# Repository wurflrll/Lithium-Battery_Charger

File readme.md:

# (Cascaded) Lithium-Ion Battery Charger 

The goals is a modular design for charging a lithium ion battery.  The board has two parts, the actual charging circuitry and the communication peripherals.

The communication peripherals includes an electrically isolated UART interface over a pulse transformer, an I2C interface to talk to the board's DAC module, and some general purpose inputs and outputs. 

Power Supply: 12V

V1 had a few issues, one was a layout error with the PIC microcontroller (I created the symbols itself in KiCad).  The other issue, much more interesting, is an issue with stability in the constant current controller.

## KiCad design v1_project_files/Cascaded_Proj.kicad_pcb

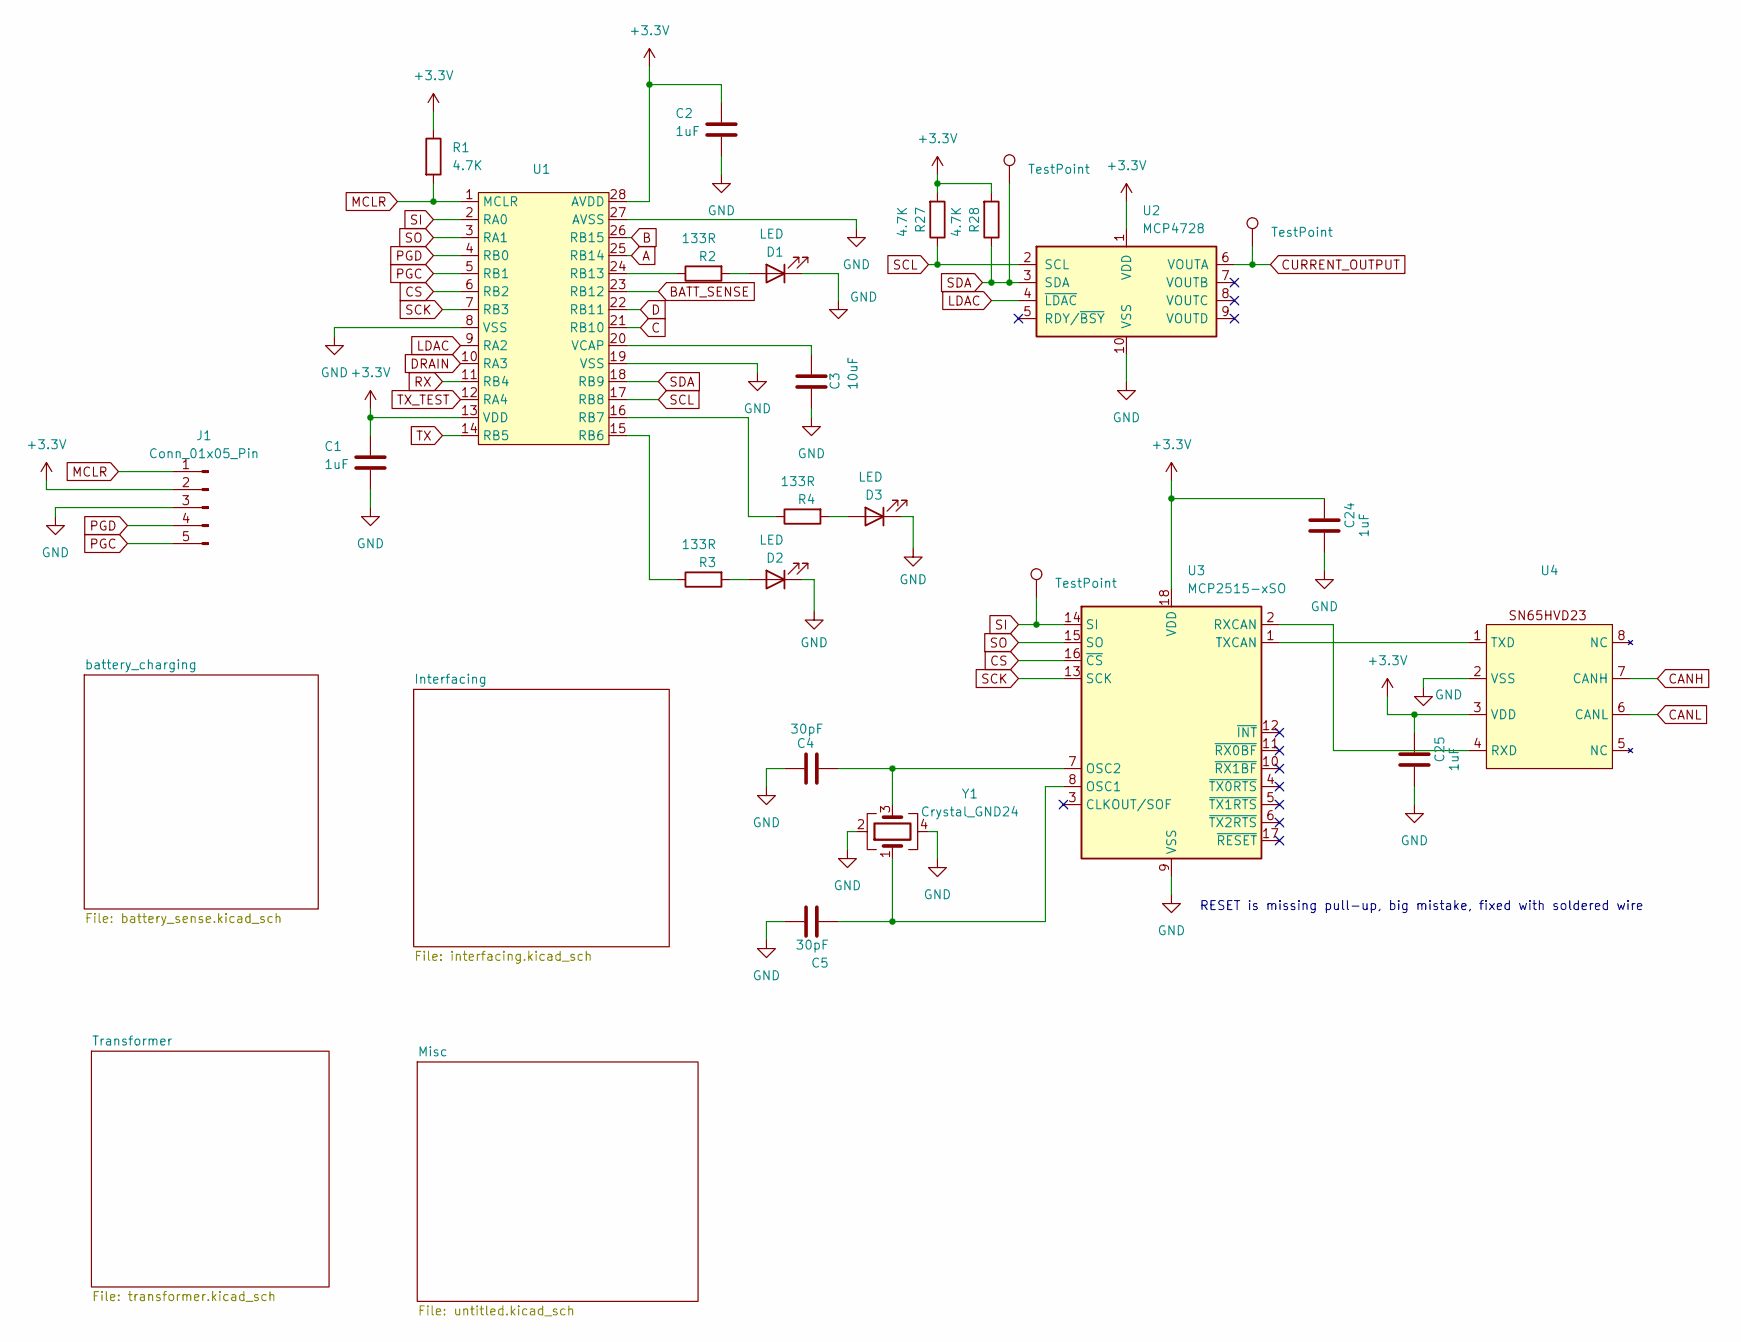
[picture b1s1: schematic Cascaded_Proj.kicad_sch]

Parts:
C1, C2, C24, C25: 1uF; C_0603_1608Metric
C3: 10uF; C_0603_1608Metric
C4, C5: 30pF; C_0603_1608Metric
D1, D2, D3: LED; LED_0805_2012Metric
J1: Conn_01x05_Pin; PinHeader_1x05_P2.54mm_Vertical
R1, R27, R28: 4.7K; R_0603_1608Metric
R2, R3, R4: 133R; R_0603_1608Metric
TP5, TP6, TP7: TestPoint; TestPoint_Plated_Hole_D2.0mm
U1: PIC24FJ64GA702
U2: MCP4728; MSOP-10_3x3mm_P0.5mm
U3: MCP2515-xSO; SOIC-18W_7.5x11.6mm_P1.27mm
U4: SN65HVD3082EDR
Y1: Crystal_GND24; Crystal_SMD_Abracon_ABM8AIG-4Pin_3.2x2.5mm

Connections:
+3.3V: C1.2, C2.2, C24.1, C25.1, J1.2, R1.1, R27.2, R28.2, U1.13 (VDD), U1.28 (AVDD), U2.1 (VDD), U3.18 (VDD), U4.3 (VDD); also elsewhere on the board
A: U1.25 (RB14); also elsewhere on the board
B: U1.26 (RB15); also elsewhere on the board
BATT_SENSE: U1.23 (RB12); also elsewhere on the board
C: U1.21 (RB10); also elsewhere on the board
CANH: U4.7 (CANH); also elsewhere on the board
CANL: U4.6 (CANL); also elsewhere on the board
CS: U1.6 (RB2), U3.16 (~CS)
CURRENT_OUTPUT: TP5.1, U2.6 (VOUTA); also elsewhere on the board
D: U1.22 (RB11); also elsewhere on the board
DRAIN: U1.10 (RA3); also elsewhere on the board
GND: C1.1, C2.1, C3.2, C4.1, C5.1, C24.2, C25.2, D1.1 (K), D2.1 (K), D3.1 (K), J1.3, U1.8 (VSS), U1.19 (VSS), U1.27 (AVSS), U2.10 (VSS), U3.9 (VSS), U4.2 (VSS), Y1.2, Y1.4; also elsewhere on the board
LDAC: U1.9 (RA2), U2.4 (~LDAC)
MCLR: J1.1, R1.2, U1.1 (MCLR)
unnamed: D1.2 (A), R2.2
unnamed: D2.2 (A), R3.2
unnamed: D3.2 (A), R4.2
unnamed: R3.1, U1.15 (RB6)
unnamed: R4.1, U1.16 (RB7)
unnamed: R2.1, U1.24 (RB13)
unnamed: C3.1, U1.20 (VCAP)
unnamed: C5.2, U3.8 (OSC1), Y1.1
unnamed: C4.2, U3.7 (OSC2), Y1.3
unnamed: U3.2 (RXCAN), U4.4 (RXD)
unnamed: U3.1 (TXCAN), U4.1 (TXD)
PGC: J1.5, U1.5 (RB1)
PGD: J1.4, U1.4 (RB0)
RX: U1.11 (RB4); also elsewhere on the board
SCK: U1.7 (RB3), U3.13 (SCK)
SCL: R27.1, U1.17 (RB8), U2.2 (SCL)
SDA: R28.1, TP6.1, U1.18 (RB9), U2.3 (SDA)
SI: TP7.1, U1.2 (RA0), U3.14 (SI)
SO: U1.3 (RA1), U3.15 (SO)
TX: U1.14 (RB5); also elsewhere on the board
TX_TEST: U1.12 (RA4); also elsewhere on the board

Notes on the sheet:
RESET is missing pull-up, big mistake, fixed with soldered wire

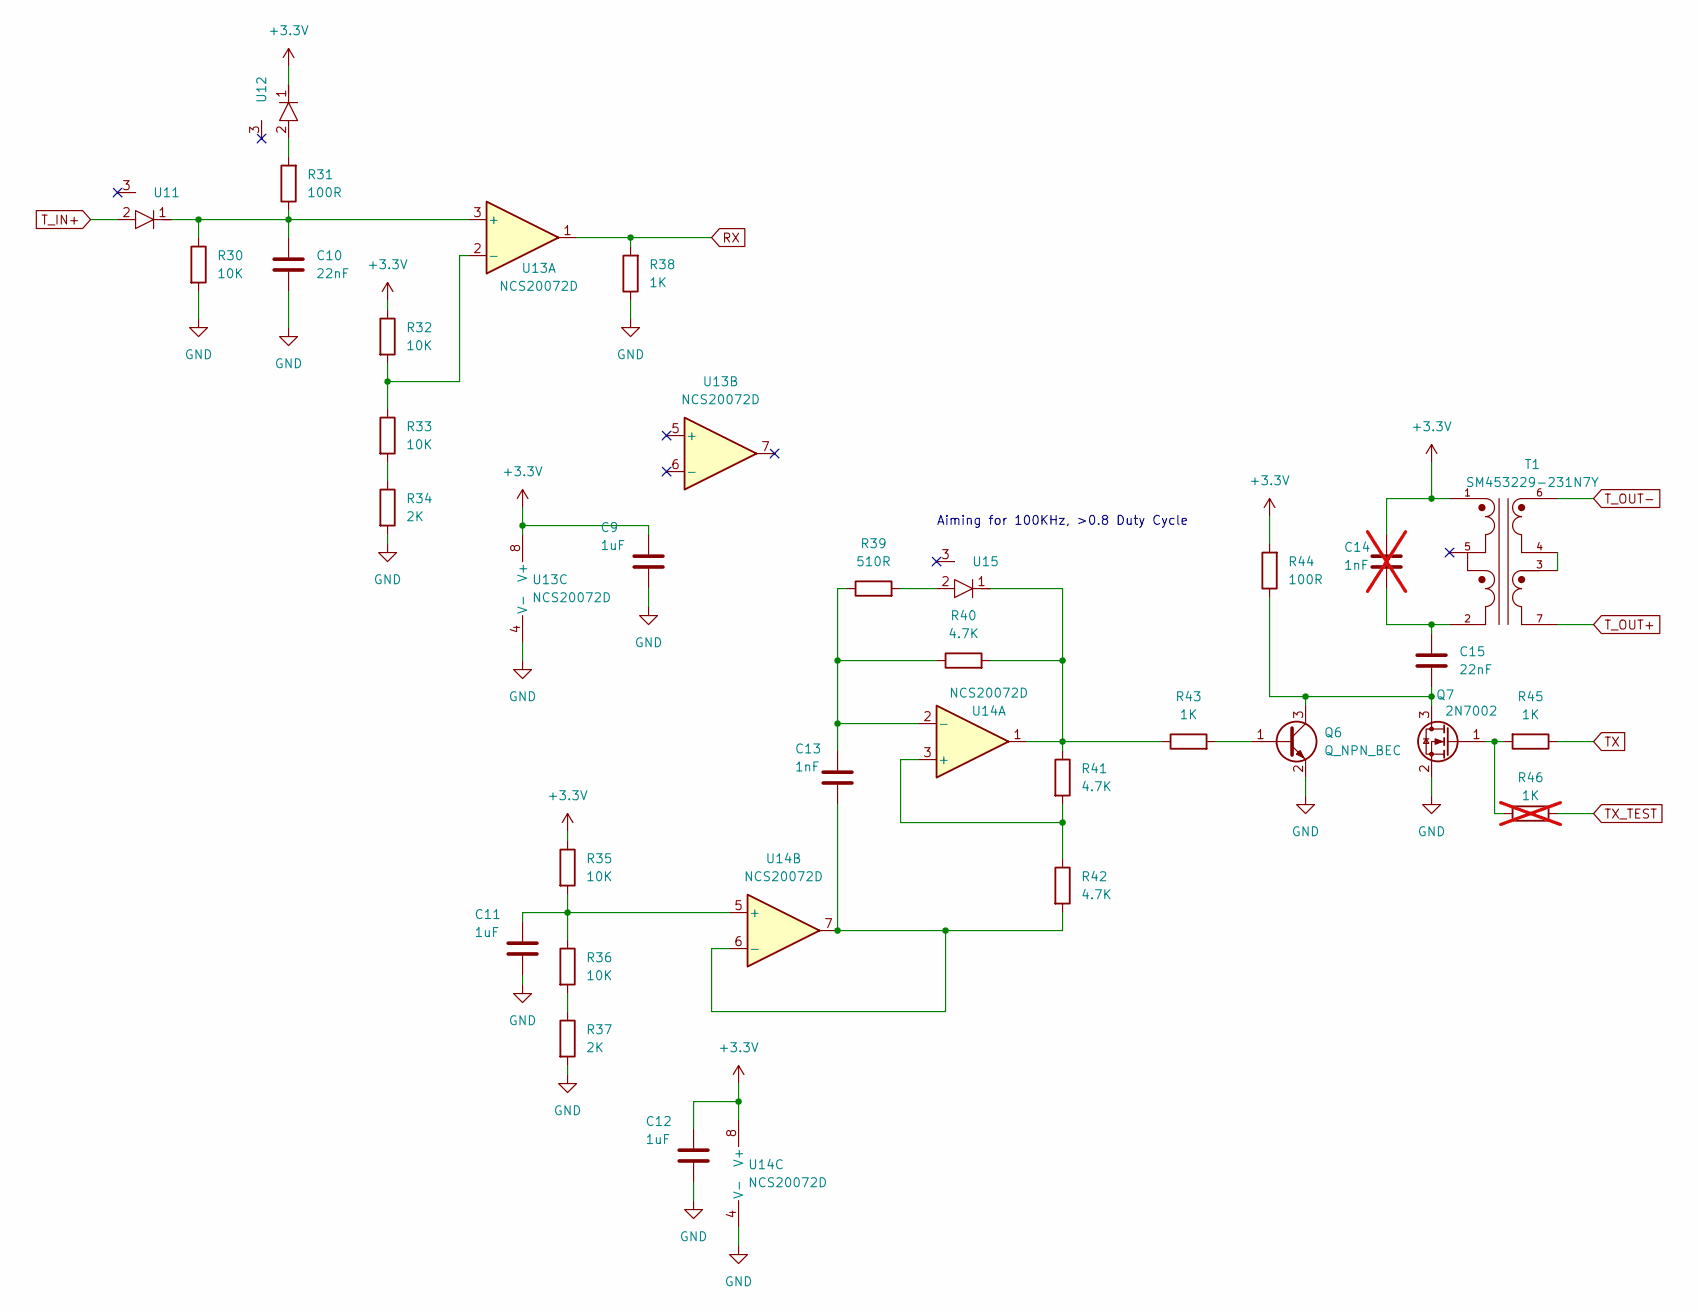
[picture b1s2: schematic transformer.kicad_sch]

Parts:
C9, C11, C12: 1uF; C_0603_1608Metric
C10, C15: 22nF; C_0603_1608Metric
C13: 1nF; C_0603_1608Metric
C14: 1nF; C_0603_1608Metric; not fitted
Q6: Q_NPN_BEC; SOT-23
Q7: 2N7002; SOT-23
R30, R32, R33, R35, R36: 10K; R_0603_1608Metric
R31, R44: 100R; R_0603_1608Metric
R34, R37: 2K; R_0603_1608Metric
R38, R43, R45: 1K; R_0603_1608Metric
R39: 510R; R_0603_1608Metric
R40, R41, R42: 4.7K; R_0603_1608Metric
R46: 1K; R_0603_1608Metric; not fitted
T1: SM453229-231N7Y
U11, U12, U15: ZLLS500TA
U13, U14: NCS20072D; SOIC-8_3.9x4.9mm_P1.27mm

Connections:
+3.3V: C9.1, C12.1, C14.1, R32.1, R35.1, R44.2, T1.1, U12.1, U13.8 (V+), U14.8 (V+); also elsewhere on the board
GND: C9.2, C10.1, C11.2, C12.2, Q6.2 (E), Q7.2 (S), R30.2, R34.2, R37.2, R38.1, U13.4 (V-), U14.4 (V-); also elsewhere on the board
unnamed: C14.2, C15.1, T1.2
unnamed: Q6.1 (B), R43.2
unnamed: C15.2, Q6.3 (C), Q7.3 (D), R44.1
unnamed: Q7.1 (G), R45.2, R46.1
unnamed: R31.2, U12.2
unnamed: R33.2, R34.1
unnamed: R36.2, R37.1
unnamed: R39.2, U15.2
unnamed: R40.2, R41.1, R43.1, U14.1, U15.1
unnamed: T1.3, T1.4
unnamed: C10.2, R30.1, R31.1, U11.1, U13.3 (+)
unnamed: R32.2, R33.1, U13.2 (-)
unnamed: R41.2, R42.1, U14.3 (+)
unnamed: C13.1, R39.1, R40.1, U14.2 (-)
unnamed: C11.1, R35.2, R36.1, U14.5 (+)
unnamed: C13.2, R42.2, U14.6 (-), U14.7
RX: R38.2, U13.1; also elsewhere on the board
TX: R45.1; also elsewhere on the board
TX_TEST: R46.2; also elsewhere on the board
T_IN+: U11.2; also elsewhere on the board
T_OUT+: T1.7; also elsewhere on the board
T_OUT-: T1.6; also elsewhere on the board

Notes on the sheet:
Aiming for 100KHz, >0.8 Duty Cycle

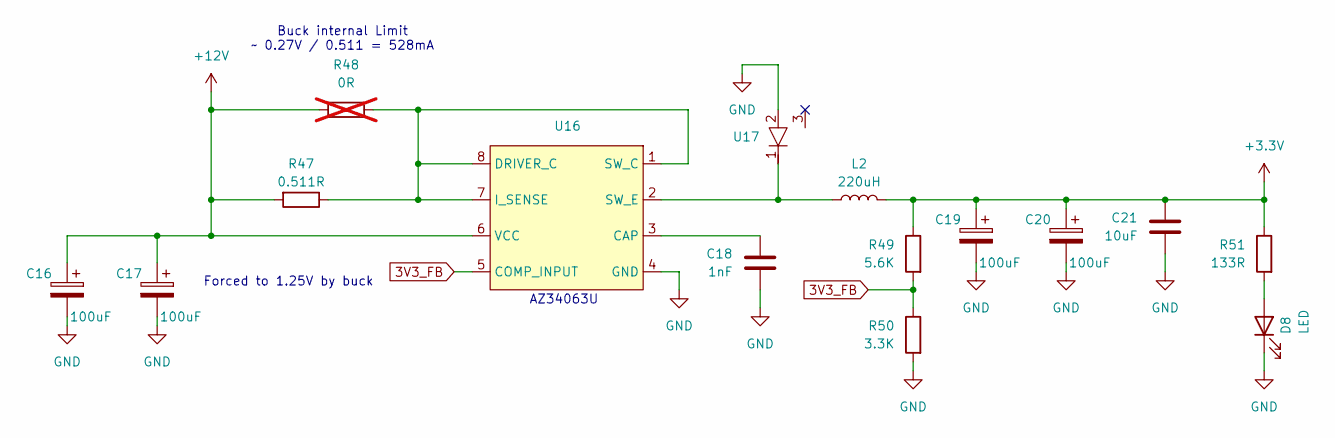
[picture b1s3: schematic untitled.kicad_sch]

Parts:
C16, C17, C19, C20: 100uF; CP_Radial_D6.3mm_P2.50mm
C18: 1nF; C_0603_1608Metric
C21: 10uF; C_0603_1608Metric
D8: LED; LED_0805_2012Metric
L2: 220uH; L_Sunlord_MWSA1205S-R36
R47: 0.511R; R_0805_2012Metric
R48: 0R; R_0805_2012Metric; not fitted
R49: 5.6K; R_0603_1608Metric
R50: 3.3K; R_0603_1608Metric
R51: 133R; R_0603_1608Metric
U16: AZ34063U
U17: ZLLS500TA

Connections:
3V3_FB: R49.2, R50.1, U16.5 (COMP_INPUT)
+3.3V: C19.1, C20.1, C21.1, L2.1, R49.1, R51.1; also elsewhere on the board
+12V: C16.1, C17.1, R47.2, R48.1, U16.6 (VCC); also elsewhere on the board
GND: C16.2, C17.2, C18.2, C19.2, C20.2, C21.2, D8.1 (K), R50.2, U16.4 (GND), U17.2; also elsewhere on the board
unnamed: D8.2 (A), R51.2
unnamed: C18.1, U16.3 (CAP)
unnamed: R47.1, R48.2, U16.1 (SW_C), U16.7 (I_SENSE), U16.8 (DRIVER_C)
unnamed: L2.2, U16.2 (SW_E), U17.1

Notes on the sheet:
AZ34063U
Forced to 1.25V by buck
Buck internal Limit ~ 0.27V / 0.511 = 528mA

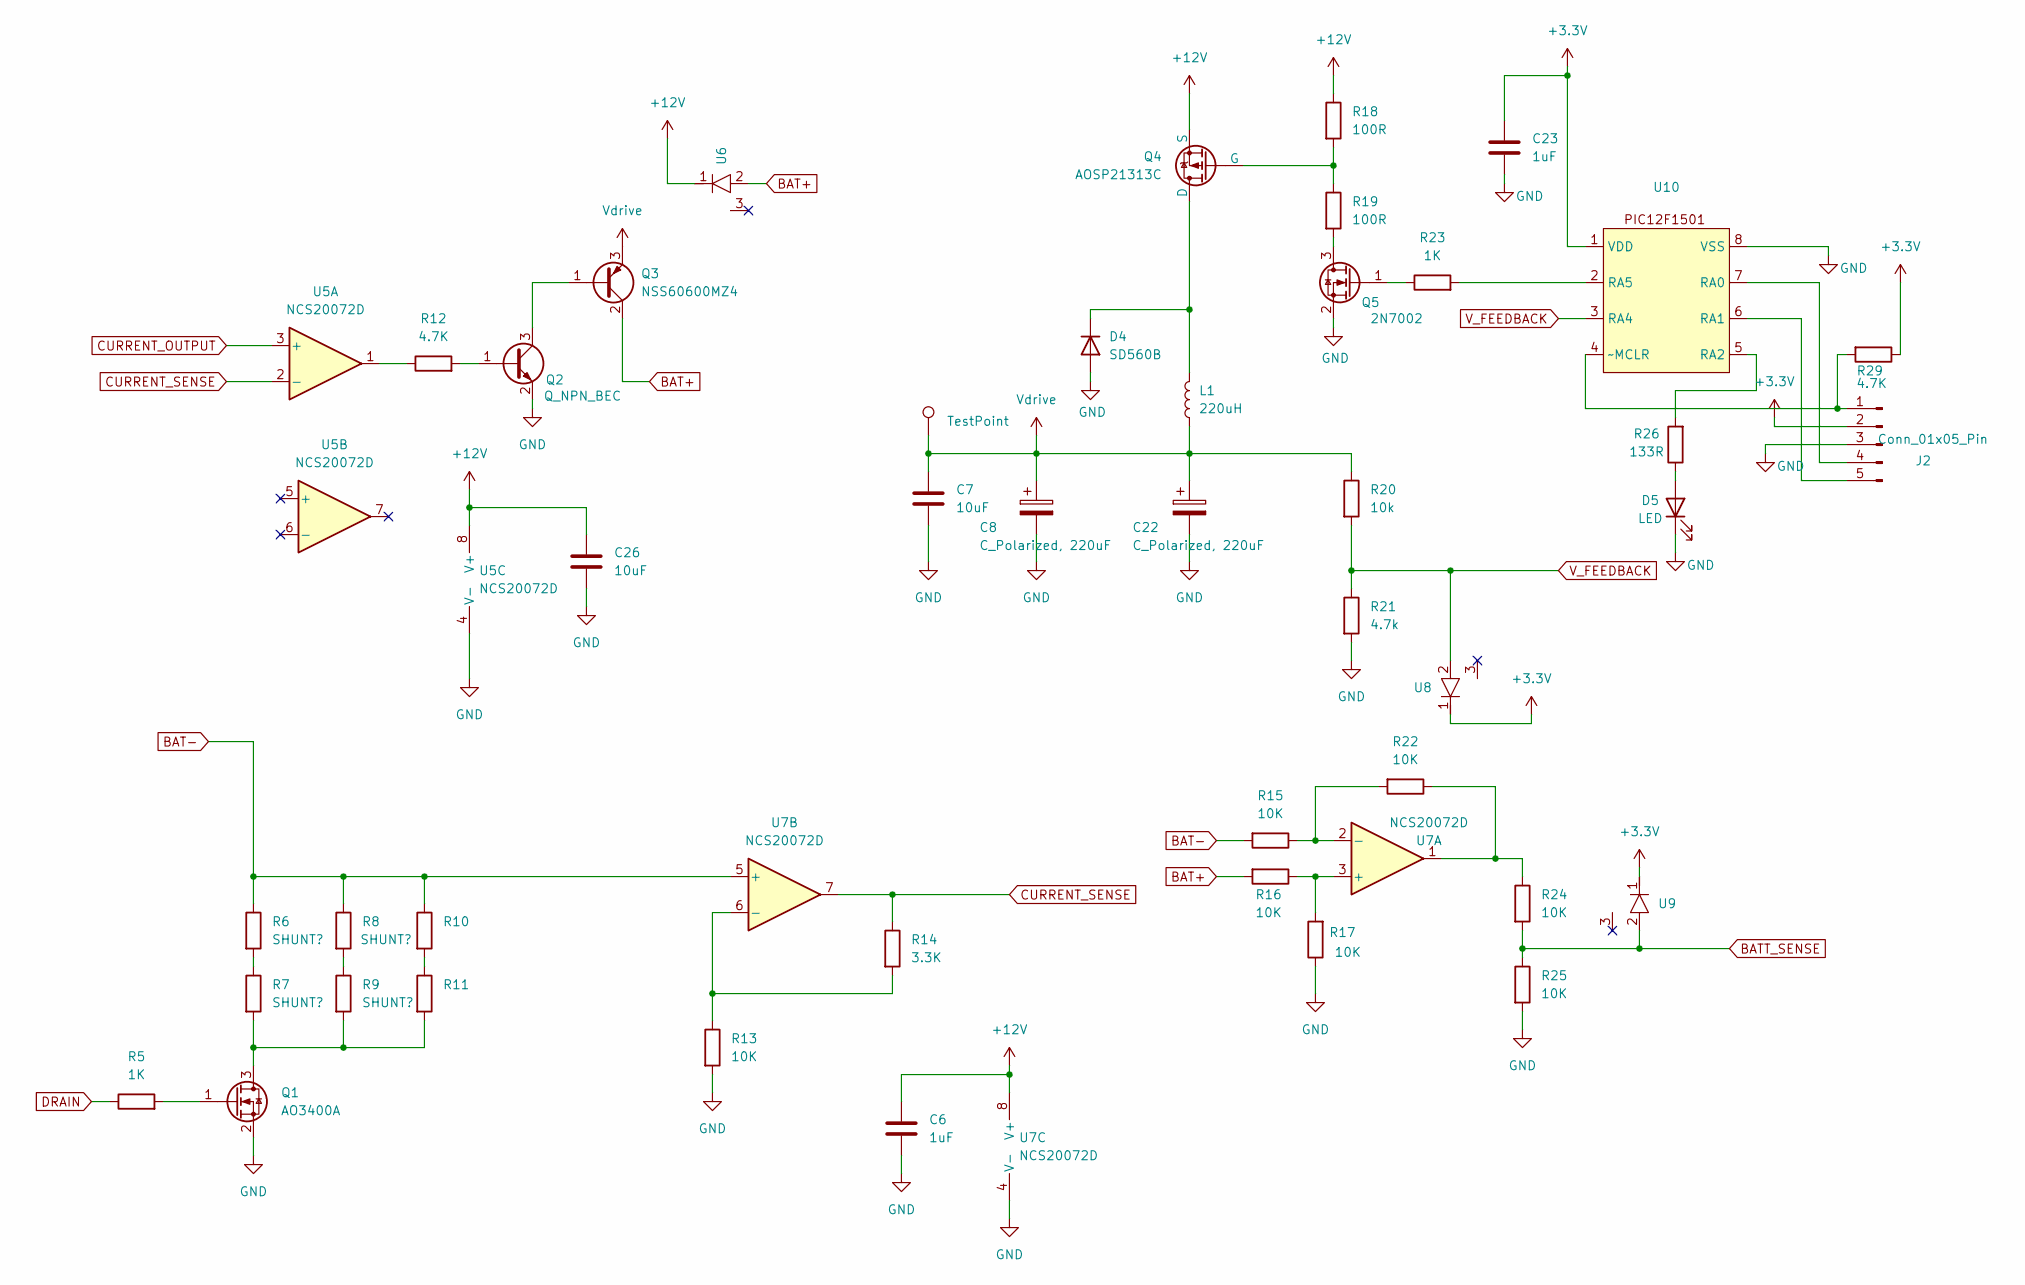
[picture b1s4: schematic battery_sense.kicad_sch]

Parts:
C6, C23: 1uF; C_0603_1608Metric
C7, C26: 10uF; C_0603_1608Metric
C8, C22: C_Polarized, 220uF; CP_Radial_D18.0mm_P7.50mm
D4: SD560B; D_MELF
D5: LED; LED_0805_2012Metric
J2: Conn_01x05_Pin; PinHeader_1x05_P2.54mm_Vertical
L1: 220uH; 2300HT-221-H-RC
Q1: AO3400A; SOT-23
Q2: Q_NPN_BEC; SOT-23
Q3: NSS60600MZ4; SOT-223-3_TabPin2
Q4: AOSP21313C
Q5: 2N7002; SOT-23
R5, R23: 1K; R_0603_1608Metric
R6, R7, R8, R9, R10, R11: SHUNT?; R_0805_2012Metric
R12, R29: 4.7K; R_0603_1608Metric
R13, R15, R16, R17, R22, R24, R25: 10K; R_0603_1608Metric
R14: 3.3K; R_0603_1608Metric
R18, R19: 100R; R_0603_1608Metric
R20: 10k; R_0603_1608Metric
R21: 4.7k; R_0603_1608Metric
R26: 133R; R_0603_1608Metric
TP3: TestPoint; TestPoint_Plated_Hole_D2.0mm
U5, U7: NCS20072D; SOIC-8_3.9x4.9mm_P1.27mm
U6, U8, U9: ZLLS500TA
U10: PIC12F1501

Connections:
+3.3V: C23.1, J2.2, R29.1, U8.1, U9.1, U10.1 (VDD); also elsewhere on the board
+12V: C6.1, C26.1, Q4.3 (S), R18.1, U5.8 (V+), U6.1, U7.8 (V+); also elsewhere on the board
BAT+: Q3.2 (C), R16.2, U6.2; also elsewhere on the board
BAT-: R6.1, R8.1, R10.1, R15.2, U7.5 (+); also elsewhere on the board
BATT_SENSE: R24.2, R25.1, U9.2; also elsewhere on the board
CURRENT_OUTPUT: U5.3 (+); also elsewhere on the board
CURRENT_SENSE: R14.1, U5.2 (-), U7.7
DRAIN: R5.1; also elsewhere on the board
GND: C6.2, C7.2, C8.2, C22.2, C23.2, C26.2, D4.2 (A), D5.1 (K), J2.3, Q1.2 (S), Q2.2 (E), Q5.2 (S), R13.2, R17.1, R21.2, R25.2, U5.4 (V-), U7.4 (V-), U10.8 (VSS); also elsewhere on the board
unnamed: D4.1 (K), L1.2, Q4.1 (D)
unnamed: D5.2 (A), R26.1
unnamed: J2.1, R29.2, U10.4 (~MCLR)
unnamed: J2.4, U10.7 (RA0)
unnamed: J2.5, U10.6 (RA1)
unnamed: Q1.3 (D), R7.2, R9.2, R11.2
unnamed: Q1.1 (G), R5.2
unnamed: Q2.1 (B), R12.2
unnamed: Q2.3 (C), Q3.1 (B)
unnamed: Q4.2 (G), R18.2, R19.1
unnamed: Q5.3 (D), R19.2
unnamed: Q5.1 (G), R23.1
unnamed: R6.2, R7.1
unnamed: R8.2, R9.1
unnamed: R10.2, R11.1
unnamed: R12.1, U5.1
unnamed: R22.1, R24.1, U7.1
unnamed: R16.1, R17.2, U7.3 (+)
unnamed: R15.1, R22.2, U7.2 (-)
unnamed: R13.1, R14.2, U7.6 (-)
unnamed: R26.2, U10.5 (RA2)
unnamed: R23.2, U10.2 (RA5)
V_FEEDBACK: R20.2, R21.1, U8.2, U10.3 (RA4)
Vdrive: C7.1, C8.1, C22.1, L1.1, Q3.3 (E), R20.1, TP3.1

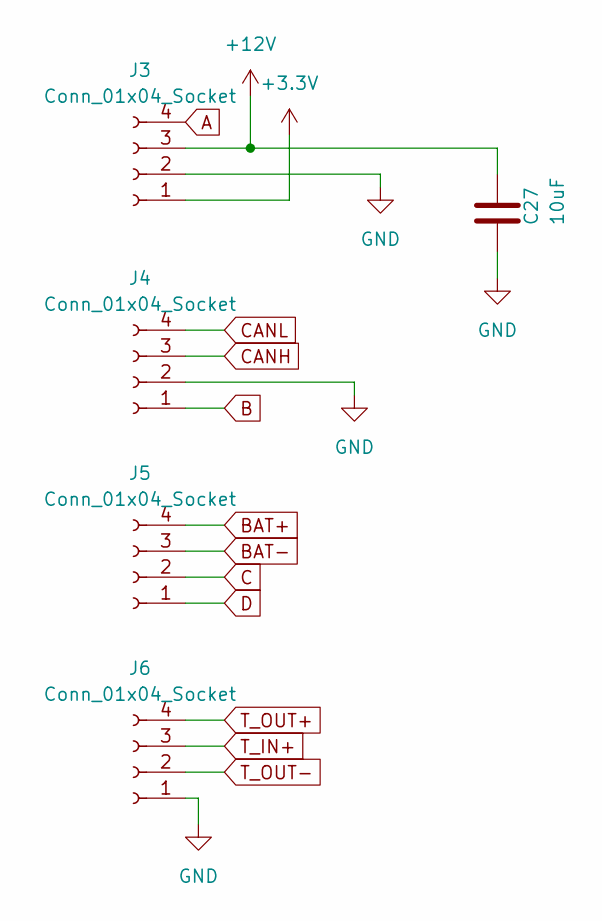
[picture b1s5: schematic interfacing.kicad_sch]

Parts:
C27: 10uF; C_0603_1608Metric
J3, J4, J5, J6: Conn_01x04_Socket; PhoenixContact_MSTBVA_2,5_4-G-5,08_1x04_P5.08mm_Vertical

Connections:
+3.3V: J3.1; also elsewhere on the board
+12V: C27.1, J3.3; also elsewhere on the board
A: J3.4; also elsewhere on the board
B: J4.1; also elsewhere on the board
BAT+: J5.4; also elsewhere on the board
BAT-: J5.3; also elsewhere on the board
C: J5.2; also elsewhere on the board
CANH: J4.3; also elsewhere on the board
CANL: J4.4; also elsewhere on the board
D: J5.1; also elsewhere on the board
GND: C27.2, J3.2, J4.2, J6.1; also elsewhere on the board
T_IN+: J6.3; also elsewhere on the board
T_OUT+: J6.4; also elsewhere on the board
T_OUT-: J6.2; also elsewhere on the board

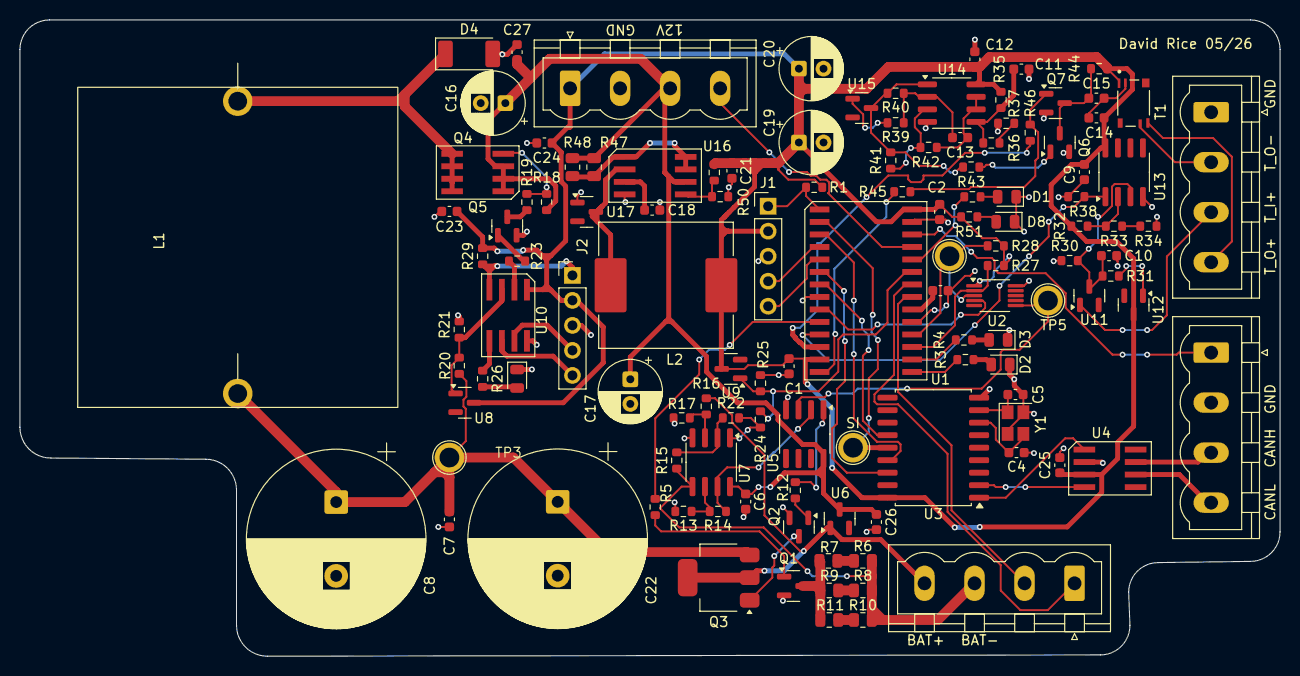
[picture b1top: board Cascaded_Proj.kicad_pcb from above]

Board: 2 copper layers, 128.0 x 64.6 mm, 122 parts (0 on the bottom side), 87 nets.

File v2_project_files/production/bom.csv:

Designator,Footprint,Quantity,Value,LCSC Part #
"C1, C11, C12, C2, C23, C24, C25, C26, C28, C6, C9",603,11,1uF,C29936 
C10,603,1,22nF,C21122 
C13,603,1,2.2nF,C107082 
"C14, C16, C17, C19, C20, C22, C8",CP_Radial_D6.3mm_P2.50mm,7,100uF,
C18,603,1,1nF,C100040 
"C21, C27, C3, C7",603,4,10uF,C96446 
"C4, C5",603,2,30pF,C113797 
"D1, D2, D3, D5, D8",805,5,LED,C19171391 
D4,D_MELF,1,SD560B,
"J1, J2, J4",PinHeader_1x05_P2.54mm_Vertical,3,Conn_01x05_Pin,
"J3, J5, J6","PhoenixContact_MSTBVA_2,5_4-G-5,08_1x04_P5.08mm_Vertical",3,Conn_01x04_Socket,
"L1, L2",L_Sunlord_MWSA1205S-R36,2,220uH,
Q1,SOT-23,1,AO3400A,C20917
"Q2, Q6",SOT-23,2,Q_NPN_BEC,C81464
Q3,SOT-223-3_TabPin2,1,NSS60600MZ4,C235754
Q4,AOSP21313C,1,AOSP21313C,
"Q5, Q7",SOT-23,2,2N7002,C916396
"R1, R11, R12, R13, R21, R27, R28, R29, R40, R41, R42",603,11,4.7K,C99782 
"R10, R23, R38, R43, R45, R46, R5, R52, R53",603,9,1K,C110776 
"R14, R15, R16, R17, R20, R22, R24, R25, R30, R32, R33, R35, R36",603,13,10K,C95204 
"R18, R19, R31, R54",603,4,100R,C122970 
"R2, R26, R3, R4, R51",603,5,133R,C5126161 
"R34, R37",603,2,2K,C844924 
R39,603,1,510R,C113299 
R47,805,1,0.511R,
R49,603,1,5.6K,C2907046 
R50,603,1,3.3K,C844928 
"R6, R7, R8, R9",805,4,SHUNT?,
"TP1, TP2, TP3, TP4, TP5, TP8, TP9",TestPoint_THTPad_2.5x2.5mm_Drill1.2mm,7,TestPoint,
U1,PIC24FJ64GA702,1,~,C641965
U10,PIC12F1501,1,~,C76411
"U11, U12, U15, U17, U18, U6, U8, U9",ZLLS500TA,8,~,C154850
"U13, U14, U5, U7",SOIC-8_3.9x4.9mm_P1.27mm,4,NCS20072D,C89845
U16,AZ34063U,1,~,C99659
U2,MSOP-10_3x3mm_P0.5mm,1,MCP4728,
U3,SOIC-18W_7.5x11.6mm_P1.27mm,1,MCP2515-xSO,C153782
U4,SN65HVD3082EDR,1,~,
Y1,Crystal_SMD_Abracon_ABM8AIG-4Pin_3.2x2.5mm,1,Crystal_GND24,C1986628

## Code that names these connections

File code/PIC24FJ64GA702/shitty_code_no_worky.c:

///*
// * File:   newmainXC16.c
// * Author: drwur
// *
// * Created on June 19, 2026, 12:18 AM
// */
//
//#define FCY 4000000UL     // Instruction clock = 4 MHz
//
//#include <xc.h>
//#include <libpic30.h>     // for __delay_ms()
//
//// Adjust to your oscillator frequency
//
//
//void I2C_Start() {
//    I2C1CONLbits.SEN = 1;         // Start condition
//    while(I2C1CONLbits.SEN);
//}
//
//void I2C_Stop() {
//    I2C1CONLbits.PEN = 1;         // Stop condition
//    while(I2C1CONLbits.PEN);
//}
//
//int I2C_ERROR() {
//    LATBbits.LATB13 = 1;
//    return 1;
//}
//
//// only takes 12 digit number
//int WriteDACvalue(uint16_t value) {  
//    uint8_t first_byte = 0x00FF & value >> 8;
//    uint8_t second_byte = value % 256;
//    
//    first_byte = 0b00000000 | first_byte; // combine with DAC bits
//
//    I2C_Start();
//            
//    // send 11000000
//    // receive ack
//    
//    I2C1TRN = 0b11000000;
//    while(I2C1STATbits.TRSTAT);
//        
//    if (I2C1STATbits.ACKSTAT) { 
//        return I2C_ERROR();
//    }
//    
//    // send 01011000 -> will automatically set output
//
//    I2C1TRN = 0b01011000;
//    while(I2C1STATbits.TRSTAT);
//        
//    if (I2C1STATbits.ACKSTAT) { 
//        return I2C_ERROR();
//    }
//       
//    // send first byte
//    I2C1TRN = first_byte;
//    while(I2C1STATbits.TRSTAT);
//        
//    if (I2C1STATbits.ACKSTAT) { 
//        return I2C_ERROR();
//    }
//    
//    I2C1TRN = second_byte;
//    while(I2C1STATbits.TRSTAT);
//        
//    if (I2C1STATbits.ACKSTAT) { 
//        return I2C_ERROR();
//    }    
//    
//    I2C_Stop();
//    return 0;
//}
//    
//
//void GeneralWrite(uint8_t data) {
//    I2C1TRN = data;
//    while(I2C1STATbits.TRSTAT);
//}
//
//
//int main(void) {
//    
//    // SDA is RB9
//    // SCL is RB8
//    // LDAC is RA2, but should be unused
//    
//    // set up error LED
//    
//#ifdef ANSB
//    ANSBbits.ANSB13 = 0;      // Disable analog function if present
//#endif
//    TRISBbits.TRISB13 = 0;    // RB13 = output
//    
//    LATBbits.LATB13 = 0;
//    
//    TRISBbits.TRISB8 = 1;   // SCL input
//    TRISBbits.TRISB9 = 1;   // SDA input
//
//    // Disable analog (if these pins have analog capability)
//    ANSELBbits.ANSB9 = 0;
//
//    ODCBbits.ODCB8 = 1; // Enable Open-Drain on SCL1 (RB8)
//    ODCBbits.ODCB9 = 1; // Enable Open-Drain on SDA1 (RB9
//    // I2C Config: 
//    
//    PMD1bits.I2C1MD = 0; // enabling I2C module
//    
//    // 1. Completely clear control registers first to reset the I2C state machine
//    I2C1CONL = 0;
//    I2C1CONH = 0;
//
//    // 2. Configure Pin Modes (RB8 is purely digital, only RB9 needs ANSEL)
//    ANSELBbits.ANSB9 = 0;   // SDA1 Pin (RB9) to Digital Mode
//    TRISBbits.TRISB8 = 1;   // SCL1 Pin (RB8) as Input
//    TRISBbits.TRISB9 = 1;   // SDA1 Pin (RB9) as Input
//
//    // 3. Set Baud Rate 
//    I2C1BRG = 18;
//
//    // 4. Enable the I2C Module LAST
//    I2C1CONLbits.I2CEN = 1;    
//    
//    TRISAbits.TRISA2 = 0;
//    LATAbits.LATA2 = 0;
//
//
//    if(I2C1CONLbits.I2CEN == 0) {
//        while(1);
//    }
//    // CALL General Reset
//    I2C_Start();
//
//    GeneralWrite(0b00000000);
//    
//    GeneralWrite(0b00000110);
//    
//    
//    I2C_Stop();
//    
//    __delay_ms(1000);
//    
//    // CALL General Wakeup
//    
//    I2C_Start();
//
//    GeneralWrite(0b00000000);
//    
//    GeneralWrite(0b00001001);
//    
//    I2C_Stop();
//    
//    __delay_ms(1000);
//
//    // Write to DAC
//    
//    while (1) {
//        WriteDACvalue(65535);
//        __delay_ms(100);
//        WriteDACvalue(0);
//    }
//            
//    return 0;
//}

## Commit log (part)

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2026-05-28 update pcb layout
